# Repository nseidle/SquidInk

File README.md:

# SquidInk
Stalwart Keypad Safe Cracking Robot
Why are we doing this?
This project of attempting to crack into the stalwart safe is not only legal, it's teachable. We are being taught how to seek out the vulnerabilities in the keypad safe using various methods and contructing robots to do so. 

Here is the website with full documentation:

https://claire0sutton.wordpress.com/category/safecracking/

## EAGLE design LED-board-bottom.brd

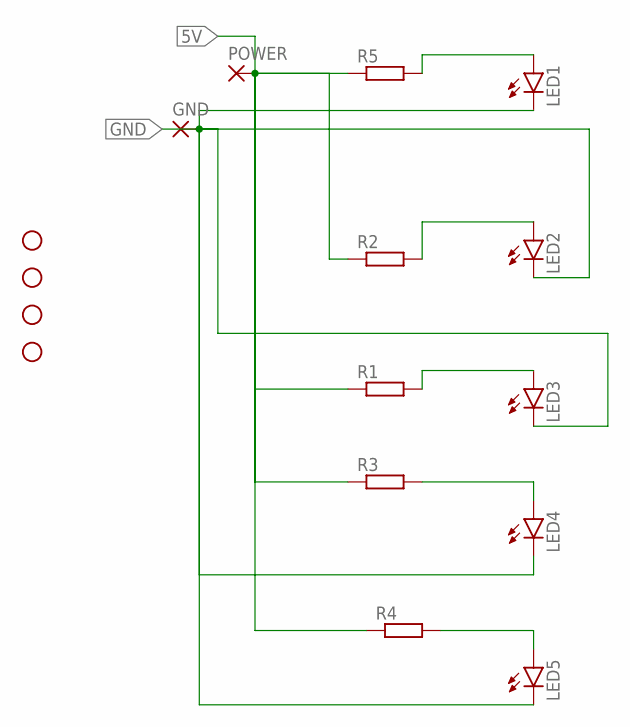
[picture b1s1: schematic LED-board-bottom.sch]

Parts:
GND: 1,6/0,8
H1, H2, H3, H4: STAND-OFF
LED1, LED2, LED3, LED4, LED5: LED3MM
POWER: 1,6/0,8
R1, R2, R3, R4, R5: R-EU_0207/10; 0207/10

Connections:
5V: POWER.1, R1.1, R2.1, R3.1, R4.1, R5.1
GND: GND.1, LED1.K (C), LED2.K (C), LED3.K (C), LED4.K (C), LED5.K (C)
unnamed: LED1.A, R5.2
unnamed: LED2.A, R2.2
unnamed: LED4.A, R3.2
unnamed: LED5.A, R4.2
unnamed: LED3.A, R1.2

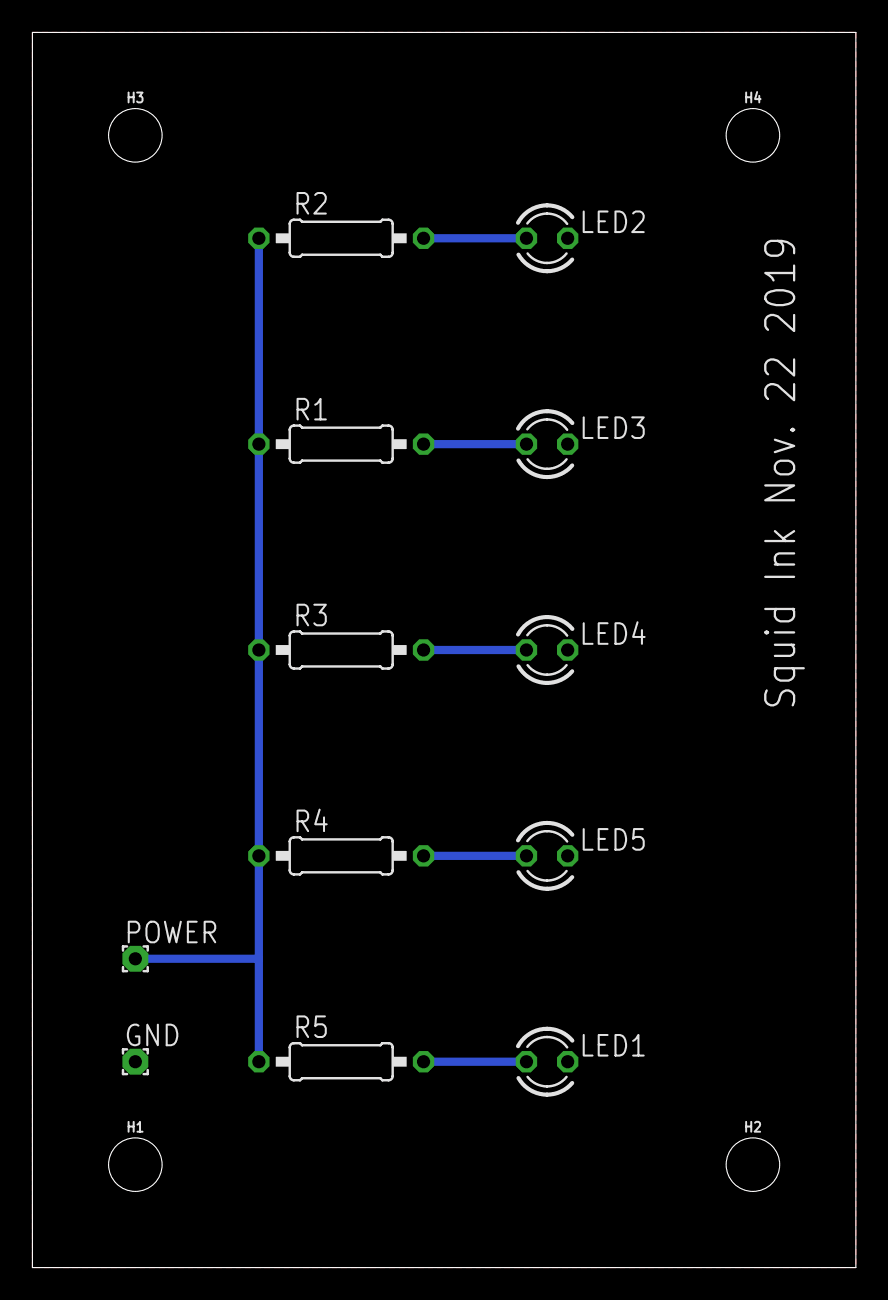
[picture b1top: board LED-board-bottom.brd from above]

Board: 2 copper layers, 50.8 x 76.2 mm, 16 parts (0 on the bottom side), 7 nets.

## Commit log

2019-09-16 Add schematic for robot controller
    Does not yet work with photogate.
2019-09-16 Removing example file class
2019-09-16 Squid Ink Pasta
    Testing my ability to upload the ink
2019-09-16 Removing Squid Pasta
2019-09-16 Safe models- Lili CQ
    This is the 3D model of the safe. The following repository includes a .3dm (editable rhino file), and interactive stl (untextured but allows the user to rotate it and look at it), and JPEG images of 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
    Why are we doing this? For our class, this modeling is necessary to aid our group in thinking in terms of the dimensions of the safe for building a robot for it.
2019-09-25 Dial Rough Draft
    Modeling the dial for coupler
2019-09-29 Motor Code
    Getting the motor to move forwards and backwards at varying speeds. Still working on the encoder
2019-09-29 dial coupler
    It is a good fit, but not as snug as it probably could be. There is no attachment for the servo motor, so it will have to wait until I can measure the attachment for it and then attach it to the coup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
2019-10-08 combined coupler draft
2019-10-16 Safe longest time
    This is my calculations for the max case scenario.
2019-11-17 Run_switch_menu
    Code that prints menu to serial monitor, asks for user input, and loops through all possibilities
    Work in progress
    Needs to be edited with switches plugged in + switch values
2019-11-18 Added Notes on Relay
2019-11-18 Updated Menu
2019-11-19 updated menu
    Can now take in input correctly. Now can parse the manually entered code and properly takes in data from the menu
2019-11-20 menu w/relay switches
    menu with relay switch code in it
2019-11-20 Using Relays Example Code
2019-11-20 Relay Switch Example Code
    Used to test the Relay Switches
2019-11-20 Menu w/Relay switches
2019-11-23 LED board bottom layer
    should be functional, may edit later
2019-12-02 Updated Menu
    tweaked variable names and fixed some comments
2019-12-02 win-state-testing
    testing the LEDs
2019-12-02 update-switch-code
2019-12-02 schematic
    schematic for relay switches. Created by Claire Sutton
2019-12-02 Updated Menu
    Servo pin was wrong
2019-12-03 Deleted file
    I don't know what this is
2019-12-04 Updated loops
    tested loop iteration and have made appropriate tweaks. Issue in printing repreatedly to the terminal. Perhaps an issue with the Serial reading going on in the menu
2019-12-05 Update menu.ino
    Now has a more accurate timing, and can trigger win state properly. Added an extra function for setting the code when also pressing the button on the inside of the safe.
2019-12-06 Realistic Worst Case Time
    In progress worst case timing .xlsx
2019-12-06 Menu update (beta)
    Uses EEPROM to store data points, currently working on a randomization code. As it is still in progress, working original code is uploaded to the master
2019-12-09 Organizing into files
    Making the github repo more organized
2019-12-09 testing EEPROM function
    yes, this is a test
2019-12-10 updated menu
    now has it so it can start from value written in to EEPROM and then return to incrementing from zero when the next value rolls around
2019-12-11 updated
    writes to EEPROM
2019-12-11 finished menu
    Now has EEPROM features, retrieves wincode and stores it in EEPROM.
    Prints code to serial monitor, if desired, but can also run unattended and on a wall wart, not plugged into a computer
2019-12-11 Squid enclosure for LEDS
2019-12-11 Worst Case Timing
2019-12-12 finished menu
    edited comments for clarity

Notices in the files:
parts and their libraries:
SparkFun-Hardware: Licensing: Creative Commons ShareAlike 4.0 International - https://creativecommons.org/licenses/by-sa/4.0
